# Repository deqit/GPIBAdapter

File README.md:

I built this adapter while poking around inside a friend’s GPIB‑to‑USB-and‑Ethernet adapters (UsbGpib v2 and GPIBee). The goal was simple: see what’s really happening on the GPIB bus without disturbing it.

The result is a fully transparent GPIB pass‑through that lets you tap every single bus line via pin headers making it easy to hook up a logic analyzer and start decoding traffic. It stays completely out of the signal path, so the device under test behaves as if nothing is there.

For quick visual feedback, ATN and REN each get their own LED. The board needs an external 5 V supply for the LEDs.

The GitHub repo includes everything you need to reproduce it: schematics, PCB files, and 3D‑printable STLs for a simple enclosure. There are caps to cover the exposed GPIB-connector-pins, to avoid accidental short circuits.

A handy little tool for anyone debugging, reverse‑engineering, or just curious about what their GPIB hardware is really saying.

This project on Hackaday.io: https://hackaday.io/project/205600-gpib-eavesdropper
More about UsbGpib v2 and GPIBee: https://github.com/xyphro/UsbGpib

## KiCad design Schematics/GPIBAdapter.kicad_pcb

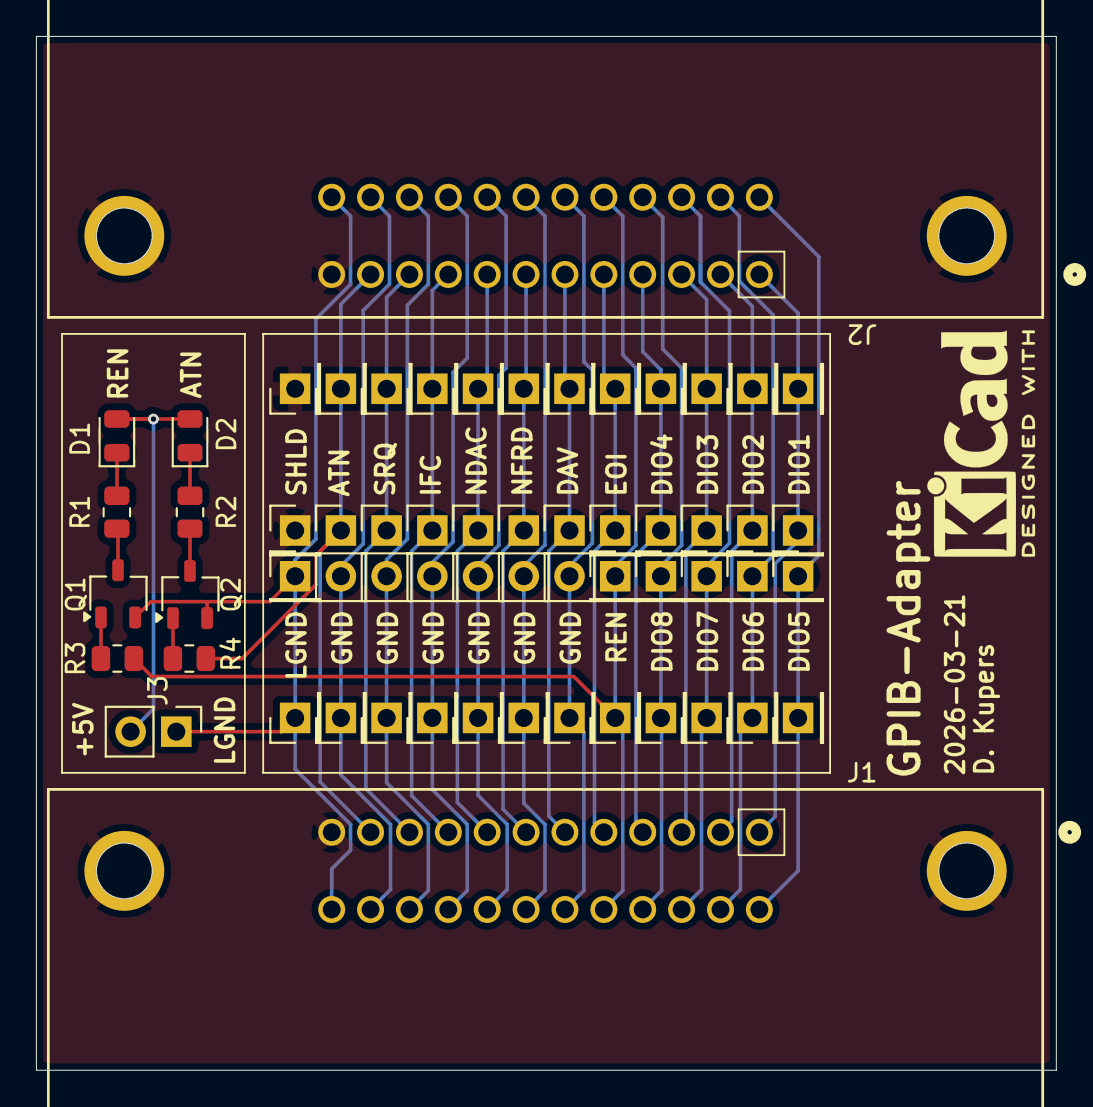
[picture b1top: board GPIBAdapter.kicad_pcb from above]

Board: 2 copper layers, 56.7 x 57.4 mm, 53 parts (0 on the bottom side), 31 nets.

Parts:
D1: LED_REN; LED_0805_2012Metric
D2: LED_ATN; LED_0805_2012Metric
J1: GPIB Centronics 24p Female; CONN_112-024-213R001_NRC (GPIB Female)
J2: GPIB Centronics 24p Male; CONN_112-024-113R001_NRC (GPIB Male)
J3, J6, J7, J8, J9, J10, J11: Conn_01x02; PinHeader_1x02_P2.54mm_Vertical
Q1, Q2: PNP; TSOT-23
R1, R2: 3k3; R_0805_2012Metric
R3, R4: 47k; R_0805_2012Metric
TP1, TP2, TP3, TP4, TP5, TP6, TP7, TP8, TP9, TP10, TP11, TP12, TP13, TP14, TP15, TP16, TP17, TP18, TP19, TP20, TP21, TP22, TP23, TP24, TP25, TP26, TP27, TP28, TP29, TP30, TP31, TP32, TP33, TP34, TP35, TP36: TestPoint; PinHeader_1x01_P2.54mm_Vertical

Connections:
+5V: D1.2 (A), D2.2 (A), J3.2
/ATN: J1.11, J2.11, J11.1, R4.1, TP23.1 (1_1)
/ATNGND: J1.23, J2.23, J11.2, TP24.1 (1_1)
/DAV: J1.6, J2.6, J6.1, TP13.1 (1_1)
/DAVGND: J1.18, J2.18, J6.2, TP14.1 (1_1)
/DIO1: J1.1, J2.1, TP3.1 (1_1), TP25.1 (1_1)
/DIO2: J1.2, J2.2, TP4.1 (1_1), TP26.1 (1_1)
/DIO3: J1.3, J2.3, TP5.1 (1_1), TP27.1 (1_1)
/DIO4: J1.4, J2.4, TP6.1 (1_1), TP28.1 (1_1)
/DIO5: J1.13, J2.13, TP7.1 (1_1), TP29.1 (1_1)
/DIO6: J1.14, J2.14, TP8.1 (1_1), TP30.1 (1_1)
/DIO7: J1.15, J2.15, TP9.1 (1_1), TP31.1 (1_1)
/DIO8: J1.16, J2.16, TP10.1 (1_1), TP32.1 (1_1)
/EOI: J1.5, J2.5, TP11.1 (1_1), TP33.1 (1_1)
/IFC: J1.9, J2.9, J9.1, TP19.1 (1_1)
/IFCGND: J1.21, J2.21, J9.2, TP20.1 (1_1)
/NDAC: J1.8, J2.8, J8.1, TP17.1 (1_1)
/NDACGND: J1.20, J2.20, J8.2, TP18.1 (1_1)
/NFRD: J1.7, J2.7, J7.1, TP15.1 (1_1)
/NRFDGND: J1.19, J2.19, J7.2, TP16.1 (1_1)
/REN: J1.17, J2.17, R3.1, TP12.1 (1_1), TP34.1 (1_1)
/SHIELD: J1.12, J1.SH (Shield), J2.12, J2.SH (Shield), TP1.1 (1_1), TP35.1 (1_1)
/SRQ: J1.10, J2.10, J10.1, TP21.1 (1_1)
/SRQGND: J1.22, J2.22, J10.2, TP22.1 (1_1)
GND: J1.24, J2.24, J3.1, Q1.2 (C), Q2.2 (C), TP2.1 (1_1), TP36.1 (1_1)
unnamed: D1.1 (K), R1.2
unnamed: D2.1 (K), R2.2
unnamed: Q1.1 (B), R3.2
unnamed: Q1.3 (E), R1.1
unnamed: Q2.1 (B), R4.2
unnamed: Q2.3 (E), R2.1

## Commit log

2026-04-17 Remove .history
2026-04-17 Deleted backups from GIT
2026-04-27 Added 3D-models of the connectors
